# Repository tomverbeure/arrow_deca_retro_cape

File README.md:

# DECA Retro Cape

**IMPORTANT: this PCB is unusuable due to an incorrect spacing between the connectors!!!**

This project is a plug-in PCB for the Arrow DECA FPGA board to extend it with the
following features:

* 2 16Mx16 SDRAMs

    Compatible with the Mister SDRAM xsds. 

* 1 PS/2 Keyboard interface

    Mouse will not work, because it's a unidirectional interface.

* 2 Atari Joystick DB9 ports 

* 1 general purupose PMOD connector

Like the SDRAM xsds board, I'm using a 5V to 3.3V LDO instead of relying on the 3V3
supply of the DECA board itself.

**Status: sent to JLCPCB. Not tested...**

# Various Notes

The information below is not always relevant, but just stuff that I gathered while
working on this PCB...

## Different Mister SDRAM Versions

Mister Addons are all designed with Altium. If you don't have a license, you can use
the Altium on-line viewer to check out schematics and PCB. I've made a screenshot of some
of them.

There are 2 main variants of SDRAM models:

1. With dedicated DQML/DQMH/CKE pins
1. With DQML/DQMH connected to A11/A12 and CKE strapped to 1.

    A11 and A12 are only used during RAS cycles, not during CAS cycles. Conversely, 
    DQML and DQMH are only during CAS cycles. So you can multi-purpose 2 pins, and thus
    save 2 pins on the connector.

    By strapping CKE to high, you can't use certain low power modes of the SDRAM, but
    that's not a major issue for a Mister-like design. However, the SDRAM datasheet
    also says that CKE must be low which VDD is being powered up, so that might
    be a violation depending on the overall power sequencing.

Because the second variant requires 3 pins less on a connector, it's now the most used option.

* [SDRAM SRAM v1.3](https://github.com/MiSTer-devel/Hardware_MiSTer/tree/master/Addons/SDRAM_SRAM)

    * 1x 16x16Mb SDRAM and 1x SRAM 8x2Mb SRAM.
    * Uses CKE to select between SDRAM and SRAM: CKE is connected SRAM.nCE.
    * Variant 1 connector.
    * Not used very often.

* [SDRAM uni 3.2U](https://github.com/MiSTer-devel/Hardware_MiSTer/tree/master/Addons/SDRAM_uni)

    * 1x 16x16Mb SDRAM
    * Variant 1 connector.

* [SDRAM xs 2.2](https://github.com/MiSTer-devel/Hardware_MiSTer/tree/master/Addons/SDRAM_xs)

    * Extra Slim (more compact than uni)
    * 1x 16x16Mb SDRAM
    * Variant 2 connector.

* [SDRAM xsd 2.5](https://github.com/MiSTer-devel/Hardware_MiSTer/tree/master/Addons/SDRAM_xsd)

    * Extra Slim, Dual-chip
    * 2x 16x16Mb SDRAM
    * All pins are shared between the 2 devices (so no double BW).
    * Variant 2 connector.
    * nCS for SDRAM2 is inverted version nCS of SDRAM1.

        This works because SDRAMs has 2 NOP commands: when nCS is high, all commands to the
        SDRAM are NOP, and when nCS is low, there's still 1 combination that's also a NOP.

* [SDRAM xsds 2.9](https://github.com/MiSTer-devel/Hardware_MiSTer/tree/master/Addons/SDRAM_xsds)

    * Extra Slim, Dual-chip
    * Logically identical to SDRAM xsd.
    * Uses DE10-Nano GPIO1 pin 11 (5V) in combination with an 
      [LM1117-3V3 LDO](https://www.ti.com/lit/ds/symlink/lm1117.pdf) to power the SDRAMs for
      higher noise resistance, instead of using GPIO1 pin 29 (3V3), which was used in all
      previous designs.

## Ferrite Bead Info

* [Analog Devices - Ferrite Beads Demystified](https://www.analog.com/media/en/technical-documentation/application-notes/AN-1368.pdf)
* [Choosing and Using Ferrite Beads](https://www.allaboutcircuits.com/technical-articles/choosing-and-using-ferrite-beads/)
* [TI - High-Speed DSP Systems Design- Reference Guide](https://www.ti.com.cn/cn/lit/ug/spru889/spru889.pdf)
* [Altium - Everything You Need to Know about Ferrite Beads](https://resources.altium.com/p/everything-you-need-to-know-about-ferrite-beads)

    Argues against its use.

## References

* [Hardware addons for MiSTer - SDR SDRAM daughter board](https://github.com/MiSTer-devel/Hardware_MiSTer#sdr-sdram-daughter-board)

    Discusses different board versions and SDRAM types, clock speeds.

    This repo also contains the Altium designs for the different add-ons. They can be viewed with the
    [Altium Online Schematic and PCB Viewer](https://www.altium.com/viewer/).

* [Addon Board Repo on GitHub](https://github.com/MiSTer-devel/Hardware_MiSTer/tree/master/Addons)

* [SDRAM Board Wiki](https://github.com/MiSTer-devel/Main_MiSTer/wiki/SDRAM-Board)

* [AS4C32M16SB-6TIN datasheet](https://www.mouser.com/datasheet/2/12/512M%20SDRAM_%20B%20die_AS4C32M16SB-7TCN-7TIN-6TIN_Rev%201-1265391.pdf)

    * [AS4C32M16SB-6TIN on Digikey](https://www.digikey.com/en/products/detail/alliance-memory-inc/AS4C32M16SB-6TIN/6716555)
    * [AS4C32M16SB-6TIN on Mouser](https://www.mouser.com/ProductDetail/913-AS4C32M16SB-6TIN)

* [Altium Online Schematic and PCB Viewer](https://www.altium.com/viewer/)

* [Mister dual-SDRAM Reliability discussion](https://misterfpga.org/viewtopic.php?t=1727)
* [SDRAM Termination discussion](https://www.electronicspoint.com/forums/threads/sdram-clock-termination.19018/)
* [SDRAM Termination discussion](https://designhelp.fedevel.com/forum/test/pcb-layout/82-sdr-sdram-layout-recommendations)
* [SDRAM Termination question on Stackexchange](https://electronics.stackexchange.com/questions/38718/termination-resistors-are-they-needed)
* [Discussion about SDRAM xsds v2.9](https://misterfpga.org/viewtopic.php?t=2480)

* [Waveshare VGA PS/2 Board](https://www.waveshare.com/vga-ps2-board.htm)

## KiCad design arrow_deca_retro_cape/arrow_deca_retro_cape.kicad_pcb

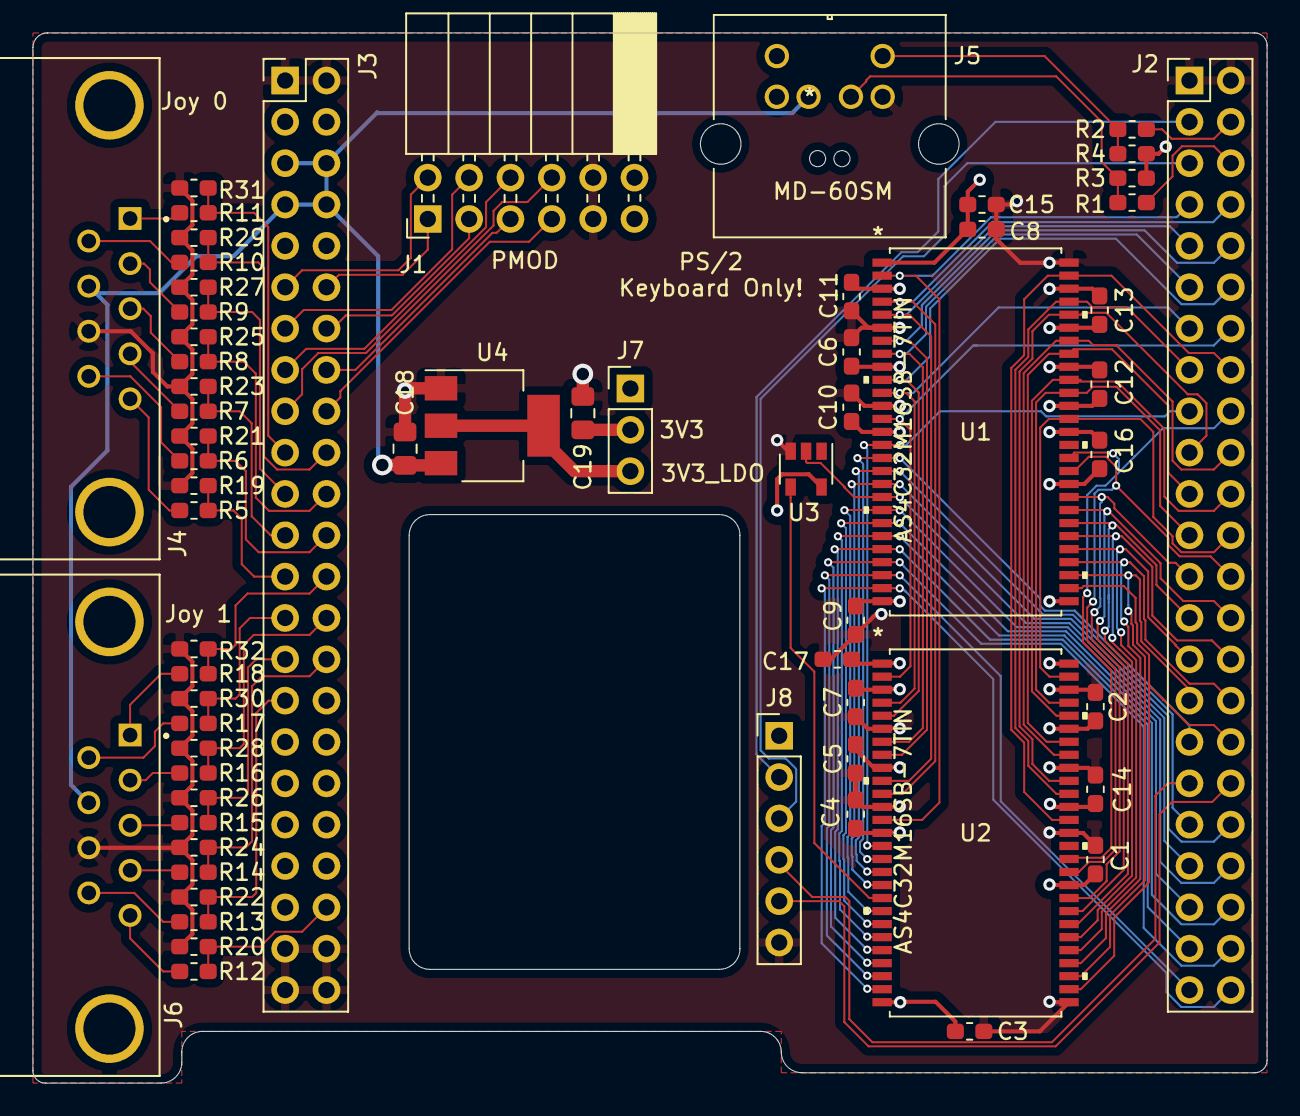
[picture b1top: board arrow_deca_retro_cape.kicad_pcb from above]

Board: 4 copper layers, 75.8 x 64.5 mm, 63 parts (0 on the bottom side), 88 nets.

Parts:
C1, C2, C3, C4, C5, C6, C7, C8, C9, C10, C11, C12, C13, C14, C15, C16, C17: 1uF; C_0603_1608Metric_Pad1.05x0.95mm_HandSolder
C18: 10uF; C_0805_2012Metric_Pad1.15x1.40mm_HandSolder
C19: 100uF; C_0805_2012Metric_Pad1.15x1.40mm_HandSolder
J1: PMOD; PMOD_Female_Horizontal
J2: P8_Male; PinHeader_2x23_P2.54mm_Vertical
J3: P9_Male; PinHeader_2x23_P2.54mm_Vertical
J4: JOY0; TE_1-1634580-2
J5: MD-60SM
J6: JOY1; TE_1-1634580-2
J7: Conn_01x03; PinHeader_1x03_P2.54mm_Vertical
J8: Conn_01x06; PinHeader_1x06_P2.54mm_Vertical
R1, R2: 1K; R_0603_1608Metric_Pad1.05x0.95mm_HandSolder
R3, R4: 10K; R_0603_1608Metric_Pad1.05x0.95mm_HandSolder
R5, R6, R7, R8, R9, R10, R11, R12, R13, R14, R15, R16, R17, R18: 2K; R_0603_1608Metric_Pad1.05x0.95mm_HandSolder
R19, R20, R21, R22, R23, R24, R25, R26, R27, R28, R29, R30, R31, R32: 5K; R_0603_1608Metric_Pad1.05x0.95mm_HandSolder
U1, U2: AS4C32M16SB-7TIN
U3: 74LVC1G04; SOT-23-5
U4: LM1117-3.3; SOT-223-3_TabPin2

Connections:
+3.3VP: J3.3, J3.4, J7.1
+3V3: C1.1, C2.1, C3.1, C4.1, C5.1, C6.1, C7.1, C8.1, C9.1, C10.1, C11.1, C12.1, C13.1, C14.1, C15.1, C16.1, C17.1, C19.1, J1.6, J1.12, J7.2, J8.1, R3.1, R4.1, U1.1, U1.3, U1.9, U1.14, U1.27, U1.37, U1.43, U1.49, U2.1, U2.3, U2.9, U2.14, U2.27, U2.37, U2.43, U2.49, U3.5
+5V: C18.1, J3.5, J3.6, J3.7, J3.8, J4.7, J5.2, J6.7, U4.3
/3V3_LDO: J7.3, U4.2
/A0: J2.43, U1.23, U2.23
/A1: J2.44, U1.24, U2.24
/A2: J2.45, U1.25, U2.25
/A3: J2.46, U1.26, U2.26
/A4: J2.34, U1.29, U2.29
/A5: J2.31, U1.30, U2.30
/A6: J2.32, U1.31, U2.31
/A7: J2.29, U1.32, U2.32
/A8: J2.30, U1.33, U2.33
/A9: J2.27, U1.34, U2.34
/A10: J2.42, U1.22, U2.22
/A11: J2.28, U1.35, U2.35
/A12: J2.25, U1.36, U2.36
/BA0: J2.40, U1.20, U2.20
/BA1: J2.41, U1.21, U2.21
/CLK: J2.26, U1.38, U2.38
/DQ0: J2.7, U1.2, U2.13
/DQ1: J2.8, U1.4, U2.11
/DQ2: J2.9, U1.5, U2.10
/DQ3: J2.10, U1.7, U2.8
/DQ4: J2.11, U1.8, U2.7
/DQ5: J2.12, U1.10, U2.5
/DQ6: J2.13, U1.11, U2.4
/DQ7: J2.14, U1.13, U2.2
/DQ8: J2.24, U1.42, U2.53
/DQ9: J2.23, U1.44, U2.51
/DQ10: J2.22, U1.45, U2.50
/DQ11: J2.21, U1.47, U2.48
/DQ12: J2.20, U1.48, U2.47
/DQ13: J2.19, U1.50, U2.45
/DQ14: J2.15, U1.51, U2.44
/DQ15: J2.16, U1.53, U2.42
/GPIO0: J2.3, J8.2
/GPIO1: J2.5, J8.3
/GPIO2: J2.35, J8.4
/GPIO3: J2.36, J8.5
/J0_DOWN: J3.21, R9.1, R27.1
/J0_LEFT: J3.22, R8.1, R25.1
/J0_PADDLE_A: J3.24, R6.1, R21.1
/J0_PADDLE_B: J3.25, R5.1, R19.1
/J0_RIGHT: J3.23, R7.1, R23.1
/J0_TRIGGER: J3.20, R10.1, R29.1
/J0_UP: J3.19, R11.1, R31.1
/J1_DOWN: J3.28, R16.1, R28.1
/J1_LEFT: J3.29, R15.1, R26.1
/J1_PADDLE_A: J3.31, R13.1, R22.1
/J1_PADDLE_B: J3.42, R12.1, R20.1
/J1_RIGHT: J3.30, R14.1, R24.1
/J1_TRIGGER: J3.27, R17.1, R30.1
/J1_UP: J3.26, R18.1, R32.1
/JOY0_DOWN: J4.2, R9.2
/JOY0_LEFT: J4.3, R8.2
/JOY0_PADDLE_A: J4.9, R6.2
/JOY0_PADDLE_B: J4.5, R5.2
/JOY0_RIGHT: J4.4, R7.2
/JOY0_TRIGGER: J4.6, R10.2
/JOY0_UP: J4.1, R11.2
/JOY1_DOWN: J6.2, R16.2
/JOY1_LEFT: J6.3, R15.2
/JOY1_PADDLE_A: J6.9, R13.2
/JOY1_PADDLE_B: J6.5, R12.2
/JOY1_RIGHT: J6.4, R14.2
/JOY1_TRIGGER: J6.6, R17.2
/JOY1_UP: J6.1, R18.2
/LDQM: J2.17, U1.15, U2.15
/PMOD_D0: J1.10, J3.17
/PMOD_D1: J1.4, J3.18
/PMOD_D2: J1.9, J3.15
/PMOD_D3: J1.3, J3.16
/PMOD_D4: J1.8, J3.13
/PMOD_D5: J1.2, J3.14
/PMOD_D6: J1.7, J3.11
/PMOD_D7: J1.1, J3.12
/PS2_CLK: J2.4, R2.2
/PS2_CLK_5V: J5.6, R2.1, R4.2
/PS2_DATA: J2.6, R1.2
/PS2_DATA_5V: J5.1, R1.1, R3.2
/UDQM: J2.18, U1.39, U2.39
/nCAS: J2.37, U1.17, U2.17
/nCS0: J2.39, U1.19, U3.2
/nCS1: U2.19, U3.4
/nRAS: J2.38, U1.18, U2.18
/nWE: J2.33, U1.16, U2.16
GND: C1.2, C2.2, C3.2, C4.2, C5.2, C6.2, C7.2, C8.2, C9.2, C10.2, C11.2, C12.2, C13.2, C14.2, C15.2, C16.2, C17.2, C18.2, C19.2, J1.5, J1.11, J2.1, J2.2, J3.1, J3.2, J3.43, J3.44, J3.45, J3.46, J4.8, J5.5, J6.8, J8.6, R19.2, R20.2, R21.2, R22.2, R23.2, R24.2, R25.2, R26.2, R27.2, R28.2, R29.2, R30.2, R31.2, R32.2, U1.6, U1.12, U1.28, U1.41, U1.46, U1.52, U1.54, U2.6, U2.12, U2.28, U2.41, U2.46, U2.52, U2.54, U3.3, U4.1

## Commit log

2021-06-16 Copy and rename pmod_cape -> retro_cape
2021-06-17 SDRAMs routed.
2021-06-19 Starting to add VGA.
2021-07-03 Layout finished.
2021-07-03 Start documenting different SDRAM blocks.
2021-07-03 Formatting.
2021-07-03 SDRAM overview.
2021-07-05 rev1, sent to JLPCB.

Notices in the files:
parts and their libraries:
Copyright 2021 Accelerated Designs. All rights reserved.
